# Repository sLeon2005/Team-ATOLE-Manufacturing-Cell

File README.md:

# 🏭 Team ATOLE Manufacturing Cell
### PLC Coordination · Computer Vision · Collaborative Robotics · IIoT Monitoring · Cybersecurity

An Industry 4.0 manufacturing cell developed at Tecnológico de Monterrey that integrates industrial automation, machine vision, collaborative robotics, Industrial IoT, cybersecurity, custom electronics, and digital manufacturing.

The system simulates an automated pastry production facility capable of:

- Identifying products using industrial vision
- Dynamically selecting manufacturing recipes
- Coordinating two Siemens PLCs through an S7 network
- Performing automated material handling with a collaborative robot
- Monitoring energy consumption in real time via MQTT
- Enforcing operator authentication through RFID access control
- Palletizing finished products automatically

---

# 📖 Project Overview

The project combines machining, industrial automation, robotics, cybersecurity, and Industrial IoT into a single integrated manufacturing system.

The complete solution is divided into two major subsystems:

## ⚙️ Plant 1 – Machining & Industrial IoT Monitoring

A custom Aluminum 6061 workpiece was designed, manufactured, and monitored during machining operations.

A custom non-invasive monitoring system measures:

- RMS current
- Active power
- Energy consumption
- Operating cost
- Machine operating state

The collected data is transmitted through MQTT and visualized in real time using a Node-RED dashboard.

---

## 🏭 Plant 2 – Automated Manufacturing Cell

The manufacturing cell is controlled by two Siemens S7-1200 PLCs interconnected through industrial Ethernet communication.

The production process includes:

1. Product classification using Cognex Vision
2. Automatic recipe selection
3. Pneumatic processing stations
4. Conveyor synchronization
5. Collaborative robotic manipulation
6. Product assembly
7. Automated palletizing

---

# 🏗️ System Architecture

The architecture integrates:

- Siemens S7-1200 PLCs
- Siemens HMIs
- Cognex Vision Sensor
- UFACTORY xArm Lite 6
- ESP32 IoT Gateway
- MQTT Broker
- Node-RED Dashboard
- RFID Authentication System
- Pneumatic Stations
- Conveyor Network

---

# 🎛️ Industrial Automation

The automation layer was implemented using two Siemens S7-1200 PLCs communicating through an S7 network.

Key features include:

- Dual PLC architecture
- Bidirectional communication
- Dynamic recipe management
- Conveyor synchronization
- Pneumatic sequencing
- HMI operation and diagnostics

---

# 👁️ Computer Vision

A Cognex industrial vision sensor acts as the cell’s quality gate.

Three reference objects are classified and mapped to production recipes:

| Object | Recipe |
|----------|----------|
| Turned Aluminum Part | Chocolate |
| Milled Aluminum Part | Strawberry |
| Metal Hook | Vanilla |

The detected classification is transmitted directly to the PLC network and automatically configures downstream process parameters.

---

# 🤖 Collaborative Robotics

A UFACTORY xArm Lite 6 collaborative robot performs:

- Raw material loading
- Inter-conveyor transfers
- Product assembly
- Palletizing

The robot was programmed in Python using the xArm SDK and operates through a Finite State Machine (FSM) architecture capable of managing multiple workpieces simultaneously.

---

# 📡 Industrial IoT Monitoring

A custom monitoring cabinet was developed around:

- ESP32
- SCT-013 Current Transformer
- ADS1115 16-bit ADC

The system continuously estimates:

- Current
- Power
- Energy
- Operating cost
- Machine utilization

without requiring direct electrical connection to the machine power circuit.

---

# 📊 MQTT & Node-RED Dashboard

Process variables are published through MQTT and visualized through a Node-RED dashboard.

Available metrics include:

- Live current consumption
- Active power
- Energy usage
- Estimated operating cost
- Machine operating state
- Historical trends

---

# 🔐 RFID Cybersecurity

An RFID authentication system was integrated to restrict access to critical HMI functions.

Only authorized operators are allowed to access or modify manufacturing parameters.

---

# 🔧 Custom Hardware Development

Several custom-designed hardware components were developed specifically for this project.

## 💻 IoT Monitoring PCB

Custom PCB for:

- Signal conditioning
- Current measurement
- ESP32 integration
- MQTT communication

---

# 🔧 Custom Hardware Development

Several custom electronic and mechanical systems were designed and fabricated specifically for this project.

## 🔐 RFID Access Control PCB

A custom PCB based on the ATmega328P was designed to provide RFID-based operator authentication.

Main features:

- ATmega328P microcontroller
- RFID card reader
- Relay outputs for PLC interfacing
- User identification system
- HMI access control

The board allows the PLC to identify authorized operators and restrict access to critical manufacturing functions.

---

## 📡 IoT Energy Monitoring System

A dedicated Industrial IoT monitoring system was developed to analyze the electrical consumption of the ROMI T240 lathe.

Hardware used:

- ESP32
- SCT-013 Current Transformer
- ADS1115 16-bit ADC
- Signal conditioning circuit

The system was implemented on a prototyping board and publishes real-time data through MQTT for remote monitoring and energy analysis.

---

## 🦾 Custom End Effectors

Custom grippers were designed and manufactured to handle:

- Raw materials
- Semi-finished products
- Finished assemblies
- Palletizing operations

---

# 🛠️ Manufacturing

## ⚙️ Custom Machined Component

A stepped Aluminum 6061 workpiece was designed in Fusion 360 and manufactured on a ROMI T240 lathe.

The part serves both as a manufactured component and as a reference object for the vision classification system.

| CAD Model | Manufactured Part |
|------------|------------|
|  |  |

---

# 🧰 Software & Engineering Tools

- Siemens TIA Portal
- Siemens Plant Simulation
- Python
- xArm SDK
- MQTT
- Mosquitto
- Node-RED
- Arduino IDE
- Fusion 360
- KiCad

---

# 📈 Results

The final system successfully demonstrated:

✅ Industrial machine vision integration

✅ Dual-PLC communication architecture

✅ Collaborative robotic manipulation

✅ Automated product assembly

✅ Automated palletizing

✅ MQTT-based Industrial IoT monitoring

✅ Real-time energy analytics

✅ RFID-based cybersecurity controls

✅ Custom electronics and PCB development

✅ End-to-end Industry 4.0 integration

---

# 👥 Team

**Team ATOLE**

Tecnológico de Monterrey, Campus Querétaro

B.S. in Mechatronics Engineering

- Kintia Alexa Negrete Osuna
- Francisco Hernández Ramírez
- Sebastián León Medellín
- Yudy Camila Pérez Cervantes
- Jesús Zamora Castelazo

---

# 📄 License

This project is licensed under the MIT License.

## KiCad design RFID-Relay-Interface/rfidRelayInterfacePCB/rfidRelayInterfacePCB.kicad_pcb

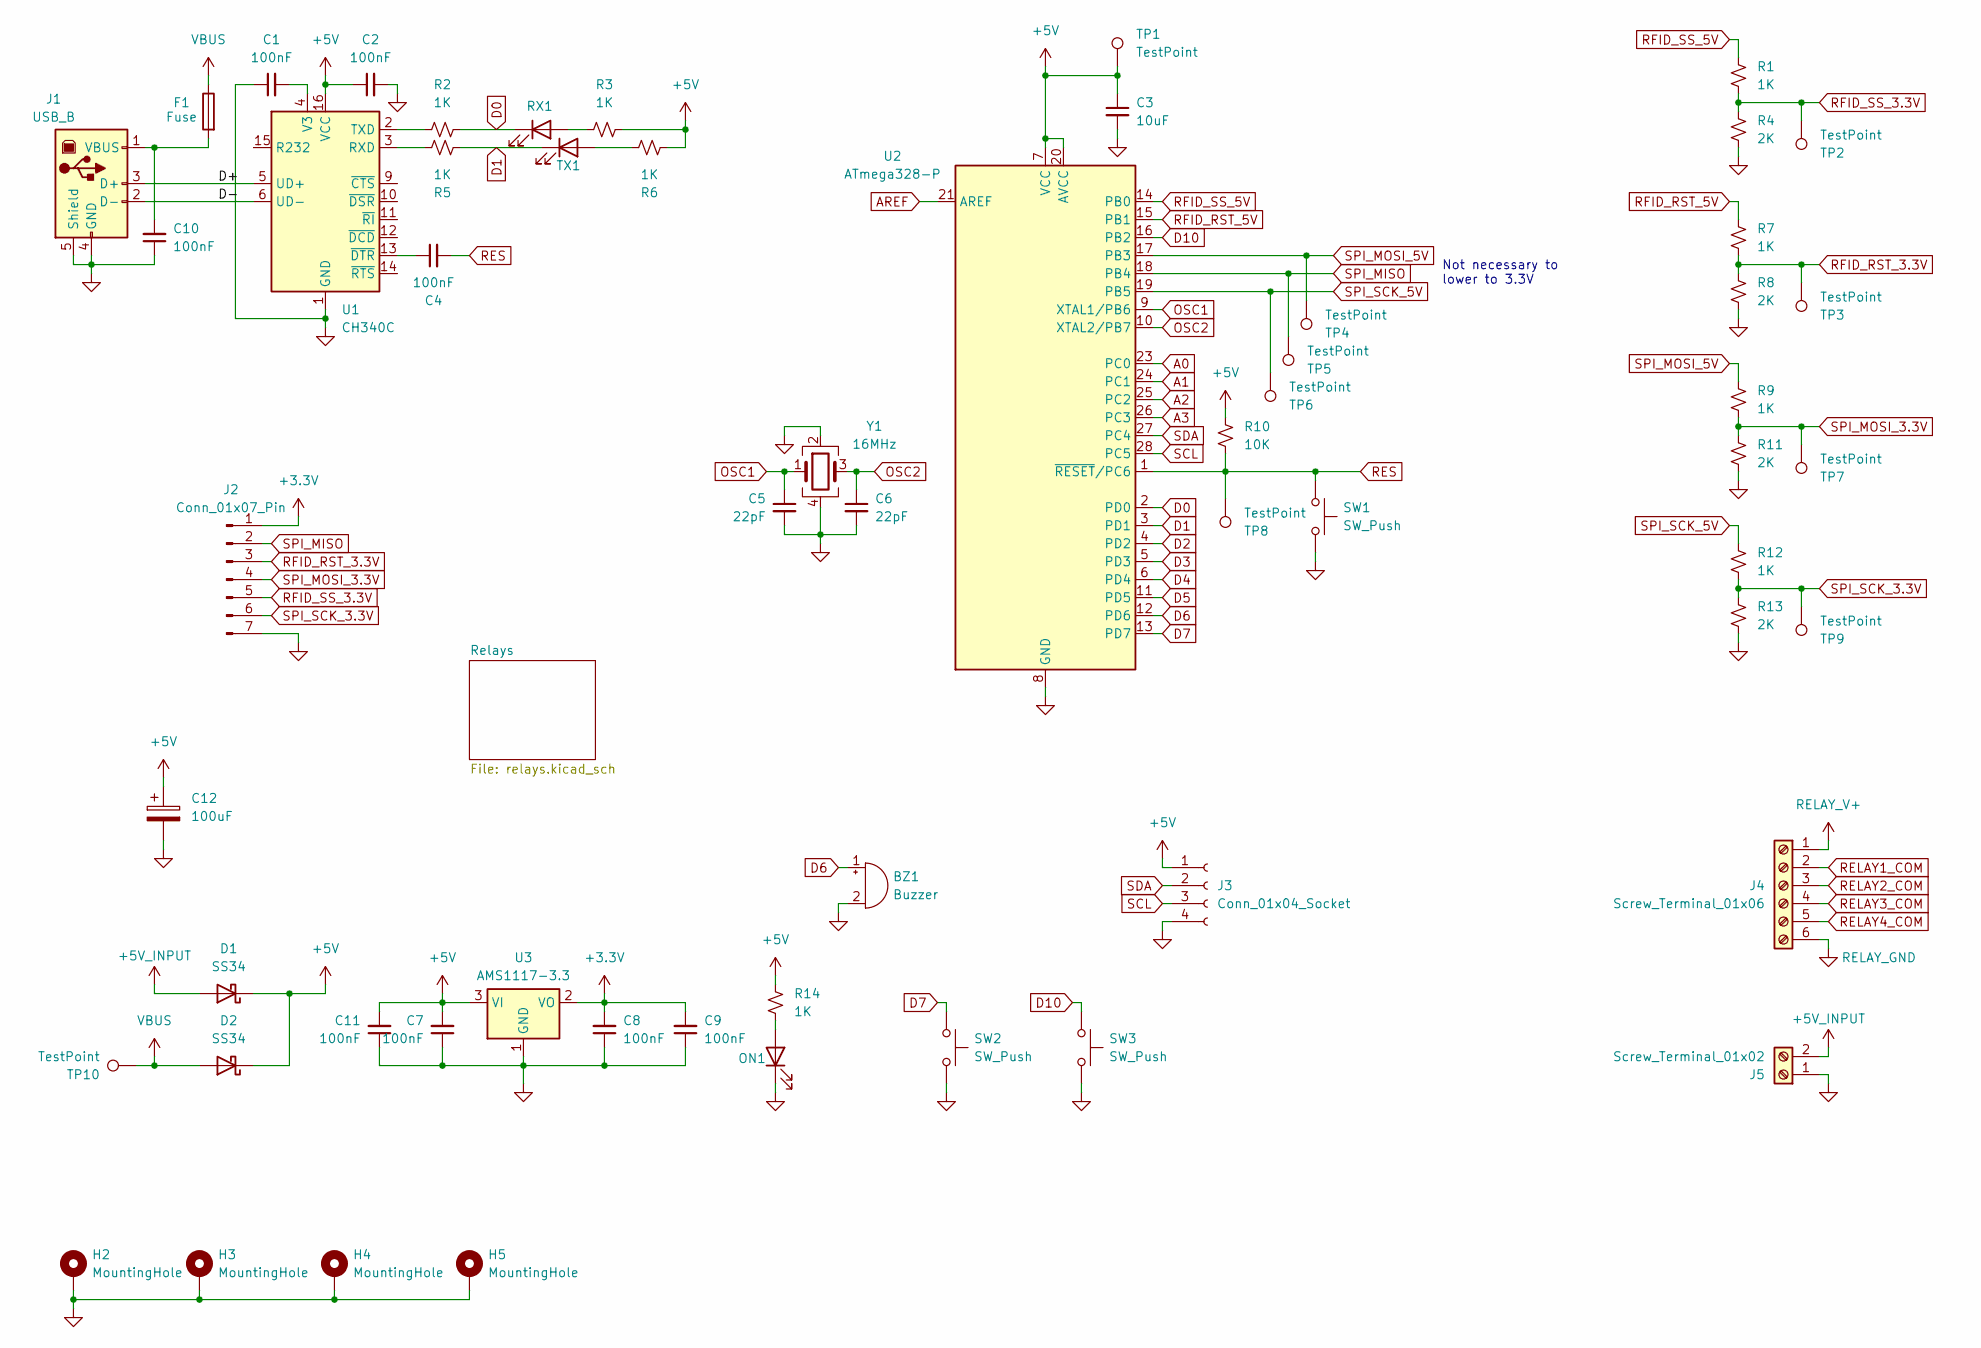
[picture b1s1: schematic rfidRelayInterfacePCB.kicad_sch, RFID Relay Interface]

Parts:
BZ1: Buzzer; Buzzer_D14mm_H7mm_P10mm
C1, C2, C4, C7, C8, C9, C10, C11: 100nF; C_0805_2012Metric_Pad1.18x1.45mm_HandSolder
C3: 10uF; C_0805_2012Metric_Pad1.18x1.45mm_HandSolder
C5, C6: 22pF; C_0805_2012Metric_Pad1.18x1.45mm_HandSolder
C12: 100uF; CP_Radial_D6.3mm_P2.50mm
D1, D2: SS34; D_SMA_Handsoldering
F1: Fuse; Fuse_1206_3216Metric_Pad1.42x1.75mm_HandSolder
H2, H3, H4, H5: MountingHole; MountingHole_3.2mm_M3_Pad_Via
J1: USB_B; USB_B_TE_5787834_Vertical
J2: Conn_01x07_Pin; PinSocket_1x07_P2.54mm_Vertical
J3: Conn_01x04_Socket; PinHeader_1x04_P2.54mm_Vertical
J4: Screw_Terminal_01x06; TerminalBlock_MaiXu_MX126-5.0-06P_1x06_P5.00mm
J5: Screw_Terminal_01x02; TerminalBlock_MaiXu_MX126-5.0-02P_1x02_P5.00mm
ON1: LED_0805_2012Metric_Pad1.15x1.40mm_HandSolder
R1, R2, R3, R5, R6, R7, R9, R12, R14: 1K; R_0805_2012Metric_Pad1.20x1.40mm_HandSolder
R4, R8, R11, R13: 2K; R_0805_2012Metric_Pad1.20x1.40mm_HandSolder
R10: 10K; R_0805_2012Metric_Pad1.20x1.40mm_HandSolder
RX1: LED_0805_2012Metric_Pad1.15x1.40mm_HandSolder
SW1, SW2, SW3: SW_Push; SW_PUSH_6mm_H5mm
TP1, TP8, TP10: TestPoint; TestPoint_THTPad_D1.5mm_Drill0.7mm
TP2, TP3, TP4, TP5, TP6, TP7, TP9: TestPoint; TestPoint_THTPad_D1.0mm_Drill0.5mm
TX1: LED_0805_2012Metric_Pad1.15x1.40mm_HandSolder
U1: CH340C; SOIC-16_3.9x9.9mm_P1.27mm
U2: ATmega328-P; DIP-28_W7.62mm_Socket_LongPads
U3: AMS1117-3.3; SOT-223-3_TabPin2
Y1: 16MHz; Crystal_SMD_3225-4Pin_3.2x2.5mm_HandSoldering

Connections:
+3.3V: C8.2, C9.2, J2.1, U3.2 (VO)
+5V: C2.1, C3.1, C7.2, C11.2, C12.1, D1.1 (K), D2.1 (K), J3.1, R3.2, R6.1, R10.1, R14.1, TP1.1, U1.16 (VCC), U2.7 (VCC), U2.20 (AVCC), U3.3 (VI); also elsewhere on the board
+5V_INPUT: D1.2 (A), J5.2
/D+: J1.3 (D+), U1.5 (UD+)
/D-: J1.2 (D-), U1.6 (UD-)
A0: U2.23 (PC0); also elsewhere on the board
A1: U2.24 (PC1)
A2: U2.25 (PC2)
A3: U2.26 (PC3)
AREF: U2.21 (AREF)
D0: R2.2, RX1.1 (K), U2.2 (PD0)
D1: R5.1, TX1.1 (K), U2.3 (PD1)
D2: U2.4 (PD2); also elsewhere on the board
D3: U2.5 (PD3); also elsewhere on the board
D4: U2.6 (PD4)
D5: U2.11 (PD5); also elsewhere on the board
D6: BZ1.1 (+), U2.12 (PD6)
D7: SW2.1, U2.13 (PD7)
D10: SW3.1, U2.16 (PB2)
GND: BZ1.2 (-), C1.1, C2.2, C3.2, C5.2, C6.2, C7.1, C8.1, C9.1, C10.1, C11.1, C12.2, H2.1, H3.1, H4.1, H5.1, J1.4 (GND), J1.5 (Shield), J2.7, J3.4, J5.1, ON1.1 (K), R4.2, R8.2, R11.2, R13.2, SW1.2, SW2.2, SW3.2, U1.1 (GND), U2.8 (GND), U2.22 (GND), U3.1 (GND), Y1.2, Y1.4; also elsewhere on the board
unnamed: C10.2, F1.2, J1.1 (VBUS)
unnamed: ON1.2 (A), R14.2
unnamed: R3.1, RX1.2 (A)
unnamed: R6.2, TX1.2 (A)
unnamed: R5.2, U1.3 (RXD)
unnamed: R2.1, U1.2 (TXD)
unnamed: C1.2, U1.4 (V3)
unnamed: C4.1, U1.13 (~DTR)
OSC1: C5.1, U2.9 (XTAL1/PB6), Y1.1
OSC2: C6.1, U2.10 (XTAL2/PB7), Y1.3
RELAY1_COM: J4.2; also elsewhere on the board
RELAY2_COM: J4.3; also elsewhere on the board
RELAY3_COM: J4.4; also elsewhere on the board
RELAY4_COM: J4.5; also elsewhere on the board
RELAY_GND: J4.6; also elsewhere on the board
RELAY_V+: J4.1; also elsewhere on the board
RES: C4.2, R10.2, SW1.1, TP8.1, U2.1 (~RESET/PC6)
RFID_RST_3.3V: J2.3, R7.2, R8.1, TP3.1
RFID_RST_5V: R7.1, U2.15 (PB1)
RFID_SS_3.3V: J2.5, R1.2, R4.1, TP2.1
RFID_SS_5V: R1.1, U2.14 (PB0)
SCL: J3.3, U2.28 (PC5)
SDA: J3.2, U2.27 (PC4)
SPI_MISO: J2.2, TP5.1, U2.18 (PB4)
SPI_MOSI_3.3V: J2.4, R9.2, R11.1, TP7.1
SPI_MOSI_5V: R9.1, TP4.1, U2.17 (PB3)
SPI_SCK_3.3V: J2.6, R12.2, R13.1, TP9.1
SPI_SCK_5V: R12.1, TP6.1, U2.19 (PB5)
VBUS: D2.2 (A), F1.1, TP10.1

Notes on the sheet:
Not necessary to lower to 3.3V

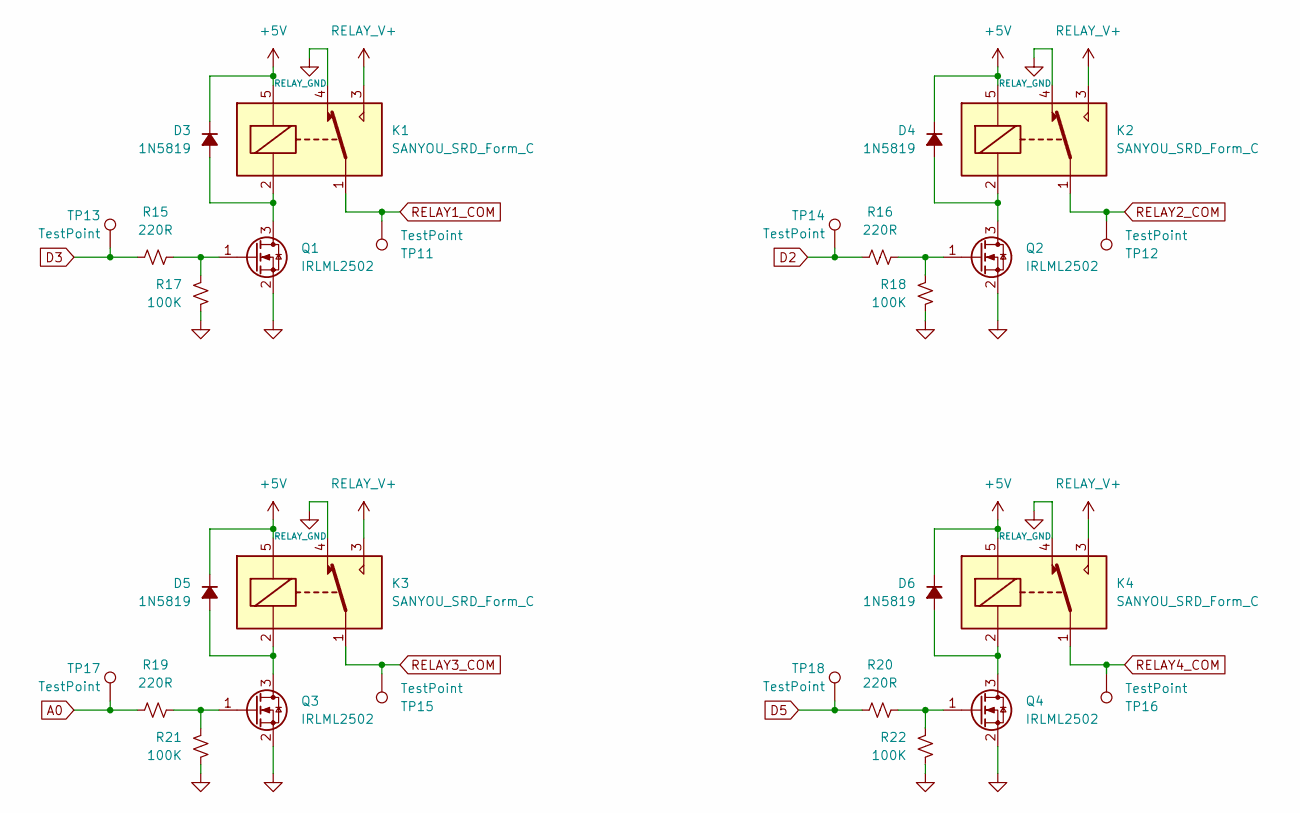
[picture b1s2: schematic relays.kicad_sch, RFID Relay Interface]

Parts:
D3, D4, D5, D6: 1N5819; D_SOD-323_HandSoldering
K1, K2, K3, K4: SANYOU_SRD_Form_C; Relay_SPDT_SANYOU_SRD_Series_Form_C
Q1, Q2, Q3, Q4: IRLML2502; SOT-23_Handsoldering
R15, R16, R19, R20: 220R; R_0805_2012Metric_Pad1.20x1.40mm_HandSolder
R17, R18, R21, R22: 100K; R_0805_2012Metric_Pad1.20x1.40mm_HandSolder
TP11, TP12, TP13, TP14, TP15, TP16, TP17, TP18: TestPoint; TestPoint_THTPad_D1.5mm_Drill0.7mm

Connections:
+5V: D3.1 (K), D4.1 (K), D5.1 (K), D6.1 (K), K1.5, K2.5, K3.5, K4.5; also elsewhere on the board
A0: R19.1, TP17.1; also elsewhere on the board
D2: R16.1, TP14.1; also elsewhere on the board
D3: R15.1, TP13.1; also elsewhere on the board
D5: R20.1, TP18.1; also elsewhere on the board
GND: Q1.2 (S), Q2.2 (S), Q3.2 (S), Q4.2 (S), R17.2, R18.2, R21.2, R22.2; also elsewhere on the board
unnamed: D3.2 (A), K1.2, Q1.3 (D)
unnamed: D4.2 (A), K2.2, Q2.3 (D)
unnamed: D5.2 (A), K3.2, Q3.3 (D)
unnamed: D6.2 (A), K4.2, Q4.3 (D)
unnamed: Q1.1 (G), R15.2, R17.1
unnamed: Q2.1 (G), R16.2, R18.1
unnamed: Q3.1 (G), R19.2, R21.1
unnamed: Q4.1 (G), R20.2, R22.1
RELAY1_COM: K1.1, TP11.1; also elsewhere on the board
RELAY2_COM: K2.1, TP12.1; also elsewhere on the board
RELAY3_COM: K3.1, TP15.1; also elsewhere on the board
RELAY4_COM: K4.1, TP16.1; also elsewhere on the board
RELAY_GND: K1.4, K2.4, K3.4, K4.4; also elsewhere on the board
RELAY_V+: K1.3, K2.3, K3.3, K4.3; also elsewhere on the board

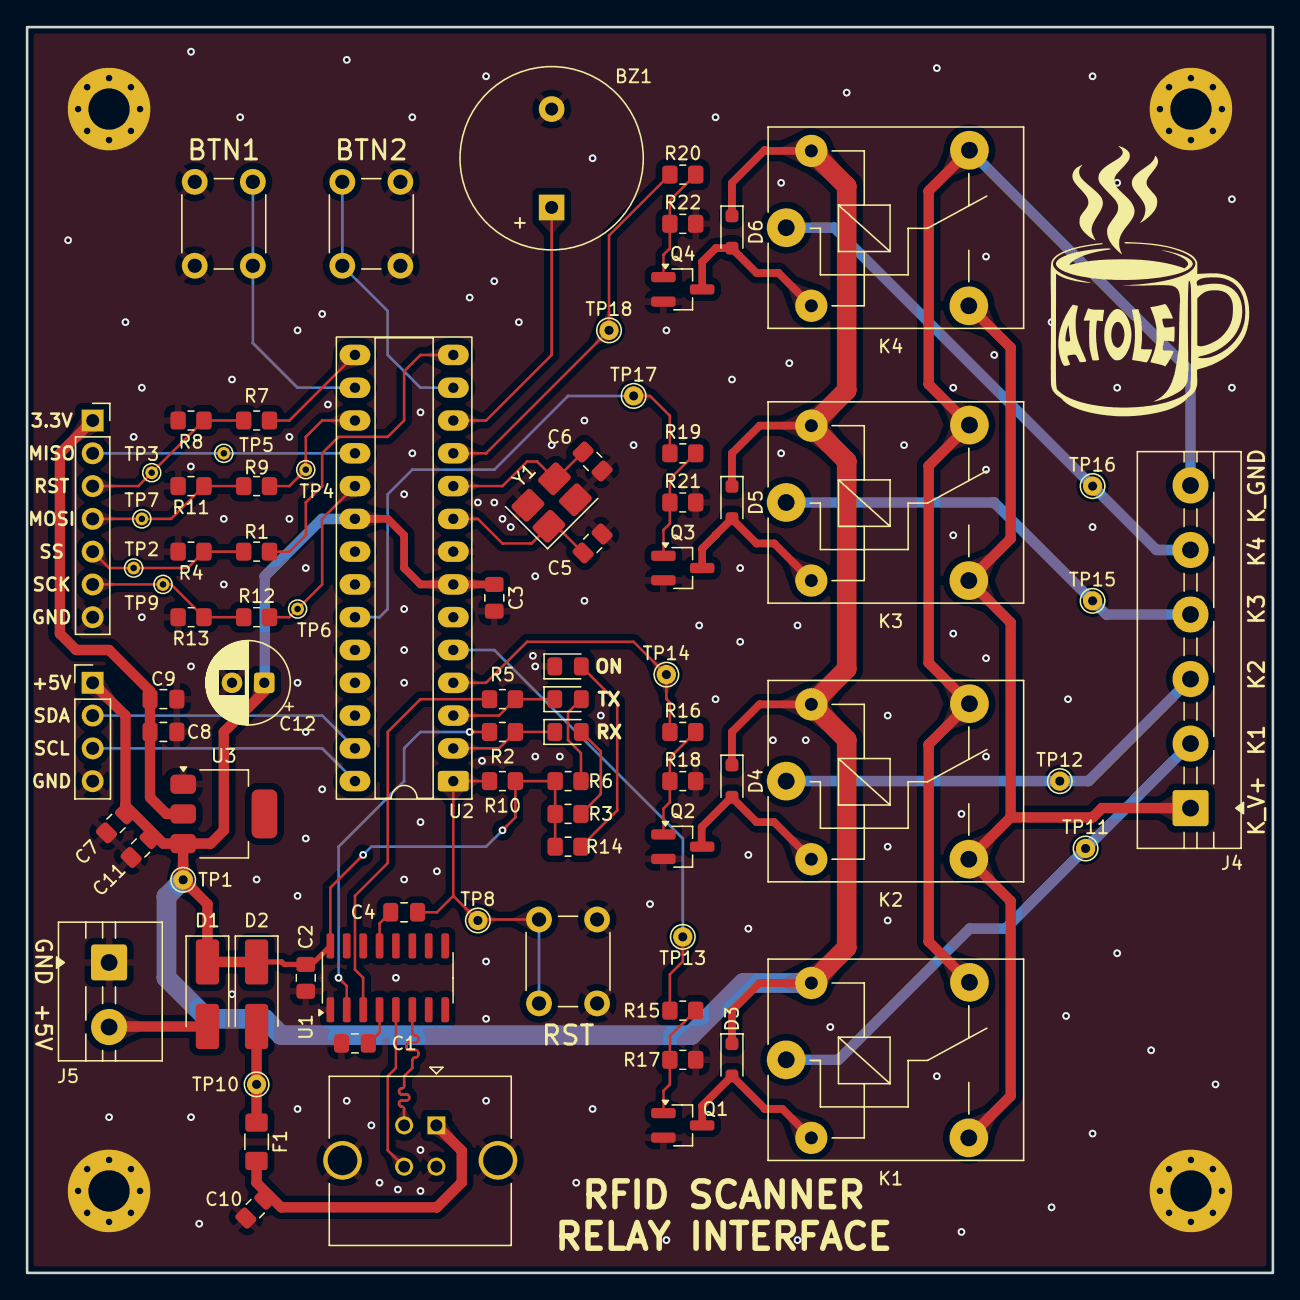
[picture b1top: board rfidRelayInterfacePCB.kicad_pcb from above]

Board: 2 copper layers, 96.5 x 96.5 mm, 87 parts (0 on the bottom side), 52 nets.

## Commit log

2026-05-14 added connection to second plc
2026-05-14 second plc
2026-05-14 second plc added with hmi
2026-05-19 Add PS folder
2026-05-19 Create Plant Simulation folder
2026-05-19 First upload of the Plant Simulation for the production line.
    It contains the first milling station.
2026-05-19 Added cobot logic
2026-05-19 Deleted duplicated file
2026-05-19 Added cobot logic. CIMA Complete
2026-05-19 Added Turntable
2026-05-20 Added Variable Processing Time Table
    Implemented in Workstation1
2026-05-20 Add file with just current sensing from instrumentation
2026-05-20 Add vision folder
2026-05-20 Added the base Cognex file
2026-05-20 Add a sketch of the electronic schematic used in the instrumentation
2026-05-20 Tried adding a 2-entrance, 2-exit method for the turntable
2026-05-20 Added 2 turntables for workstation1
2026-05-20 Corrected turntables orientation and angle
2026-05-20 Fixed current sensing
2026-05-21 tweaked pneumatic hmi
2026-05-21 Redid vision system, fixed flash, moved zoom
2026-05-21 Changed the project to english
2026-05-21 Moved the PLC files to another folder, added tag tables
2026-05-21 Changed A LOT of stuff...
2026-05-21 last bit
2026-05-21 Current sensor code with comments
2026-05-21 Current sensor code that publishes data via MQTT
2026-05-22 al chile demasiadas cosas ya ni sé que
    si
2026-05-22 Improved logic
2026-05-22 Added all conveyor and worstation logic up to polishing station
2026-05-22 Added Converter Logic
2026-05-22 Approved by teacher
2026-05-22 Approved by teacher
    It was approved by teacher. Be aware that you have to go to the Inputs/Outputs option in the software, change the 3rd output to Programmed and change the time to 500 ms
2026-05-22 Added sorter and inspection stations
2026-05-22 Queue working fine in machining
2026-05-25 Added power consumption, basic cobot comm
2026-05-25 Started Working on an Assembly Method
2026-05-25 Created an Assembly station with 3 different Assemblies based on Main_Mu
2026-05-25 Added packing station
2026-05-25 Check just aesthetics and shipping before Final Version
2026-05-25 Added the link from PLC to MQTT (PC as gateway)
2026-05-25 Separate the ip's from the public project
2026-05-25 example ip's
2026-05-25 added pycache to gitignore
2026-05-26 improved cobot logic
2026-05-26 Update PLC and MQTT configuration parameters
2026-05-26 improved gitignore
2026-05-26 Changed mechanical pusher stations to turntables/angular converters
2026-05-26 Added Bus Transport
2026-05-28 finished code for rfid relay interface
2026-05-28 add .step files of 3d printed files used in didactic cell
2026-05-28 fixed gitignore config.py
2026-05-28 Corrected Assembly Stations according to professor
2026-05-28 added example ip's file
2026-05-28 Added pcb files
2026-05-28 Final Approved Logic by professor
2026-05-28 RFID case 3D models
2026-05-28 Palletizing 3D models .step
2026-05-28 Added files for RFID case in .STEP
2026-05-28 Added files for palletizing mold in .STEP
2026-05-28 Added some visual decorative elements
2026-05-28 Pneu HMI with access
2026-05-28 RFID Acces is working now, more data to be added
2026-05-28 Add files via upload
    Added more pictures, BE AWARE: choose "programado" in the Inputs/Outputs section and set to 500ms the times of outputs
2026-05-29 Added some topics based on the algebraic sum of other acquired values
2026-05-29 PUT-GET communication completed, pneu screen permits done
2026-05-29 python gateway db ready with values
2026-05-29 Added tutorial and role address/topic
2026-05-29 donde for the day
2026-05-29 FINAL VERSION
2026-05-29 Added palet base 3x3 in .STEP
2026-05-29 Added verified topics to publish to
2026-05-29 Add files via upload
    More pictures, approved by teacher, in the Inputs/Outputs area be shure that all 3 outputs are in "Programmed" and change their times to 500ms
2026-05-29 cobot integration stronger, should send palletizing bits with fifo
2026-05-29 RFID access completed, cobot logic nearly completed, cobot FIFO completed
2026-06-01 added power consumption in MXN
2026-06-01 created a folder for cobot code
2026-06-01 Update currentSensing.ino
    Current (A), Power (kW), Energy (kWh) and Cost ($ MXN)
2026-06-01 Update ATOLE_cobot.py
    Final Version (Palletizing Test Pending)
2026-06-02 update tag excel tables
2026-06-02 erase cobot try project
2026-06-02 change name of folder
2026-06-02 Attempt to improve the cobot communication for sending palletizing byte
2026-06-02 Update ATOLE_cobot.py
    Updated Bits for Palletizing
2026-06-02 added assets
2026-06-03 Manufactured piece data & insights
    ROMI T-240 (CIMA)
    June 2nd, 2026
2026-06-03 Add Kintia's uuid and shorten Fran's name
2026-06-04 Update ATOLE_cobot.py
    Palletizing error pending
2026-06-04 cobot send logic finished, missing cycle time and count pieces
2026-06-05 Update ATOLE_cobot.py
    Adapted Comments in english and deleted waypoint after lid assembly
2026-06-05 FINAL Reviewed Version
    Just to make sure nothing is missing. Report section complete
2026-06-05 Update ATOLE_cobot.py
    Added measurements to prevent SDK not responding
2026-06-05 Update ATOLE_cobot.py
    Corrected Bits sent to cobot after palletizing logic
2026-06-05 add topic for the cognex id
2026-06-05 Update ATOLE_cobot.py
    Changed time.sleep after sending bits to Cobot
2026-06-05 Update ATOLE_cobot.py
    Adjusted Velocities - WORKING FOR VIDEO
2026-06-05 plc code for friday video
2026-06-05 sorry
2026-06-08 Version FINAL
2026-06-08 reset fifo on logout, palletizing busy, cycle time screen
2026-06-08 Update ATOLE_cobot.py
    Added gripper off
2026-06-09 Update simple_cobot_code.py
    Version ready to test
2026-06-09 tuesday 9 morning version
2026-06-10 working version wednesday morning
2026-06-10 Update ATOLE_cobot.py
    WORKING FINAL
2026-06-10 Update gripperON-OFF_WIP.py
    We tried to implement a method to deactivate the gripper at points where it is not actively being used to grasp or transport parts.
2026-06-10 Revise README for Team ATOLE Manufacturing Cell
    Updated project name and enhanced README content to provide a comprehensive overview of the Team ATOLE Manufacturing Cell, including system architecture, features, and team details.
2026-06-10 Improve README formatting and add emojis
    Updated README.md to enhance formatting and add emojis for better readability.
2026-06-10 pcb pic
2026-06-10 Improve image display for RFID PCB
    Updated image formatting for RFID PCB in README.
